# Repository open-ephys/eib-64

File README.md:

# EIB-64
64-channel electrode interface board (EIB) with electrical and optical
stimulation. Designed for small animal (e.g. mouse) tetrode electrophysiology.
Compatible with [ONIX 64-Channel Headstage](https://github.com/open-ephys/onix-headstage-64) and [Shuttle
Drives](https://open-ephys.org/shuttledrive).

See [this spreadsheet](https://docs.google.com/spreadsheets/d/1WYDymxNqGRtFPxn69H9JzeMgePpXcFSPHiWJYBE0lu4/edit?usp=sharing) for channel map 

- 64x electrophysiology channels
- 2x optical stimulation outputs
- 1x electrical stimulator output

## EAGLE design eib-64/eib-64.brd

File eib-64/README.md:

# EIB-64 PCB
Circuit design and manufacturing files for EIB-64.

## Bill of Materials
The BOM is located on [this google
sheet](https://docs.google.com/spreadsheets/d/1vJ3K68Tzy18eBl7zj2bWWYmF2zrh3wpJbKvRicM5Wa0/edit?usp=sharing)

## Pinout
The EIB pinout (ADC input mapping, stimulation connections, etc) is located on
[this google
sheet](https://docs.google.com/spreadsheets/d/11wRDYOqHN5lPb03yUdfXfK0zvaDYsVetplaNK-R90Gg/edit#gid=0)

## Tetrode Connectorization
This EIB uses Neuralynx ["small" gold
pins](https://neuralynx.com/hardware/small-eib-pins) to attach tetrode wires.
Usage instructions are provided in the [Neuralynx EIB pin
Manual](https://neuralynx.com/documents/EIB%20Pins%20Manual.pdf).

## Manufacturing Requirments
- 4 layer PCB (outer layers provide sheilding)
- 0.6-0.8 mm total thickness
- Immersion gold plating (ENIG) is required. 
- In order for the gold pins to properly fit in the designated vias, they must
  have a _plated_ inner diameter of 12±2 mil (0.3048±0.0508 mm).

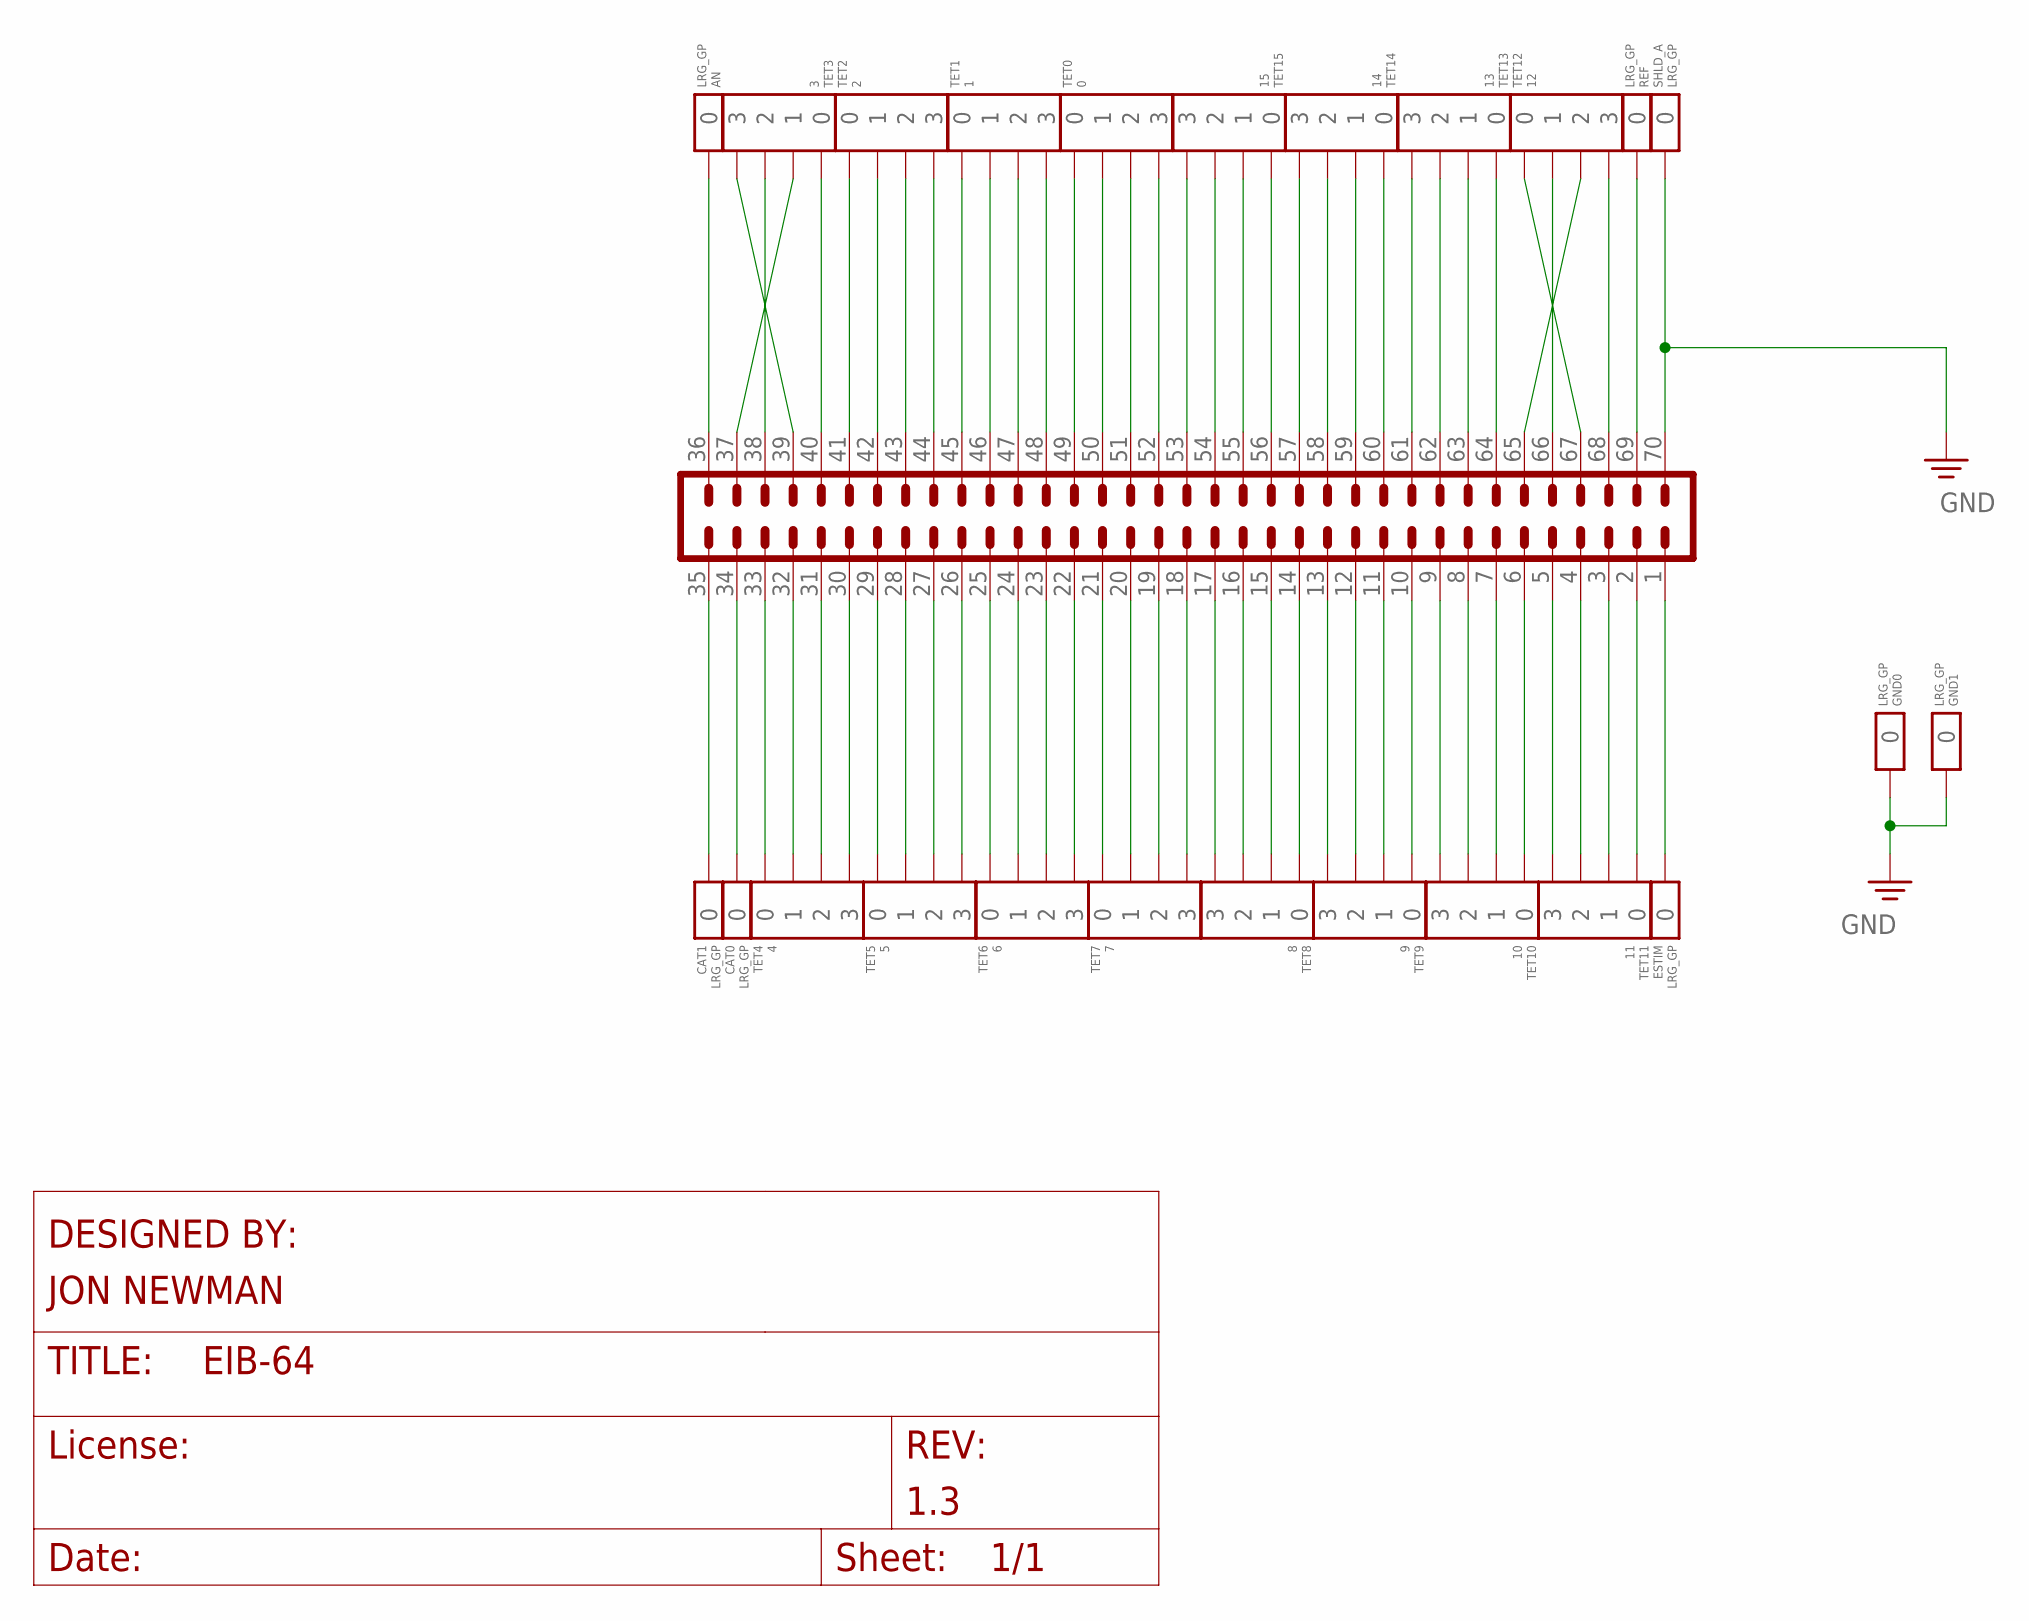
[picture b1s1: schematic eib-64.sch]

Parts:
AN: LRG_GP; GOLDPIN_0.5ID_0.7OD
CAT0, CAT1: LRG_GP; GOLDPIN_0.5ID_0.7OD
ESTIM: LRG_GP; GOLDPIN_0.5ID_0.7OD
GND0, GND1: LRG_GP; GOLDPIN_0.5ID_0.7OD
J1: DF40-REC; DF40-70REC
REF: LRG_GP; GOLDPIN_0.5ID_0.7OD
SHLD_A: LRG_GP; GOLDPIN_0.5ID_0.7OD
TET0: 0; TETRODE_0.3ID_LINEAR_MOUSE
TET1: 1; TETRODE_0.3ID_LINEAR_MOUSE
TET2: 2; TETRODE_0.3ID_LINEAR_MOUSE
TET3: 3; TETRODE_0.3ID_LINEAR_MOUSE
TET4: 4; TETRODE_0.3ID_LINEAR_MOUSE
TET5: 5; TETRODE_0.3ID_LINEAR_MOUSE
TET6: 6; TETRODE_0.3ID_LINEAR_MOUSE
TET7: 7; TETRODE_0.3ID_LINEAR_MOUSE
TET8: 8; TETRODE_0.3ID_LINEAR_MOUSE
TET9: 9; TETRODE_0.3ID_LINEAR_MOUSE
TET10: 10; TETRODE_0.3ID_LINEAR_MOUSE
TET11: 11; TETRODE_0.3ID_LINEAR_MOUSE
TET12: 12; TETRODE_0.3ID_LINEAR_MOUSE
TET13: 13; TETRODE_0.3ID_LINEAR_MOUSE
TET14: 14; TETRODE_0.3ID_LINEAR_MOUSE
TET15: 15; TETRODE_0.3ID_LINEAR_MOUSE

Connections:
AN: AN.P$1, J1.36
CAT0: CAT0.P$1, J1.34
CAT1: CAT1.P$1, J1.35
ESTIM: ESTIM.P$1, J1.1
GND: GND0.P$1, GND1.P$1, J1.70, SHLD_A.P$1
unnamed: J1.68, TET12.3
unnamed: J1.65, TET12.2
unnamed: J1.66, TET12.1
unnamed: J1.67, TET12.0
unnamed: J1.64, TET13.0
unnamed: J1.63, TET13.1
unnamed: J1.62, TET13.2
unnamed: J1.61, TET13.3
unnamed: J1.60, TET14.0
unnamed: J1.59, TET14.1
unnamed: J1.58, TET14.2
unnamed: J1.57, TET14.3
unnamed: J1.56, TET15.0
unnamed: J1.55, TET15.1
unnamed: J1.54, TET15.2
unnamed: J1.53, TET15.3
unnamed: J1.52, TET0.3
unnamed: J1.51, TET0.2
unnamed: J1.50, TET0.1
unnamed: J1.49, TET0.0
unnamed: J1.48, TET1.3
unnamed: J1.47, TET1.2
unnamed: J1.46, TET1.1
unnamed: J1.45, TET1.0
unnamed: J1.44, TET2.3
unnamed: J1.43, TET2.2
unnamed: J1.42, TET2.1
unnamed: J1.41, TET2.0
unnamed: J1.40, TET3.0
unnamed: J1.39, TET3.3
unnamed: J1.38, TET3.2
unnamed: J1.37, TET3.1
unnamed: J1.5, TET11.3
unnamed: J1.4, TET11.2
unnamed: J1.3, TET11.1
unnamed: J1.2, TET11.0
unnamed: J1.33, TET4.0
unnamed: J1.32, TET4.1
unnamed: J1.31, TET4.2
unnamed: J1.30, TET4.3
unnamed: J1.29, TET5.0
unnamed: J1.28, TET5.1
unnamed: J1.27, TET5.2
unnamed: J1.26, TET5.3
unnamed: J1.25, TET6.0
unnamed: J1.24, TET6.1
unnamed: J1.23, TET6.2
unnamed: J1.22, TET6.3
unnamed: J1.21, TET7.0
unnamed: J1.20, TET7.1
unnamed: J1.19, TET7.2
unnamed: J1.18, TET7.3
unnamed: J1.17, TET8.3
unnamed: J1.16, TET8.2
unnamed: J1.15, TET8.1
unnamed: J1.14, TET8.0
unnamed: J1.13, TET9.3
unnamed: J1.12, TET9.2
unnamed: J1.11, TET9.1
unnamed: J1.10, TET9.0
unnamed: J1.9, TET10.3
unnamed: J1.8, TET10.2
unnamed: J1.7, TET10.1
unnamed: J1.6, TET10.0
REF: J1.69, REF.P$1

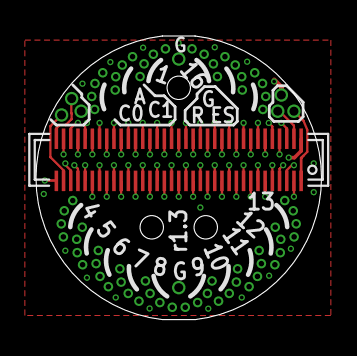
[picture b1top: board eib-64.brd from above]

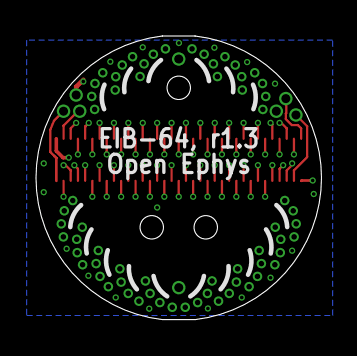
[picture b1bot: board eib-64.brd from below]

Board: 4 copper layers, 15.9 x 15.8 mm, 25 parts (8 on the bottom side), 70 nets.
